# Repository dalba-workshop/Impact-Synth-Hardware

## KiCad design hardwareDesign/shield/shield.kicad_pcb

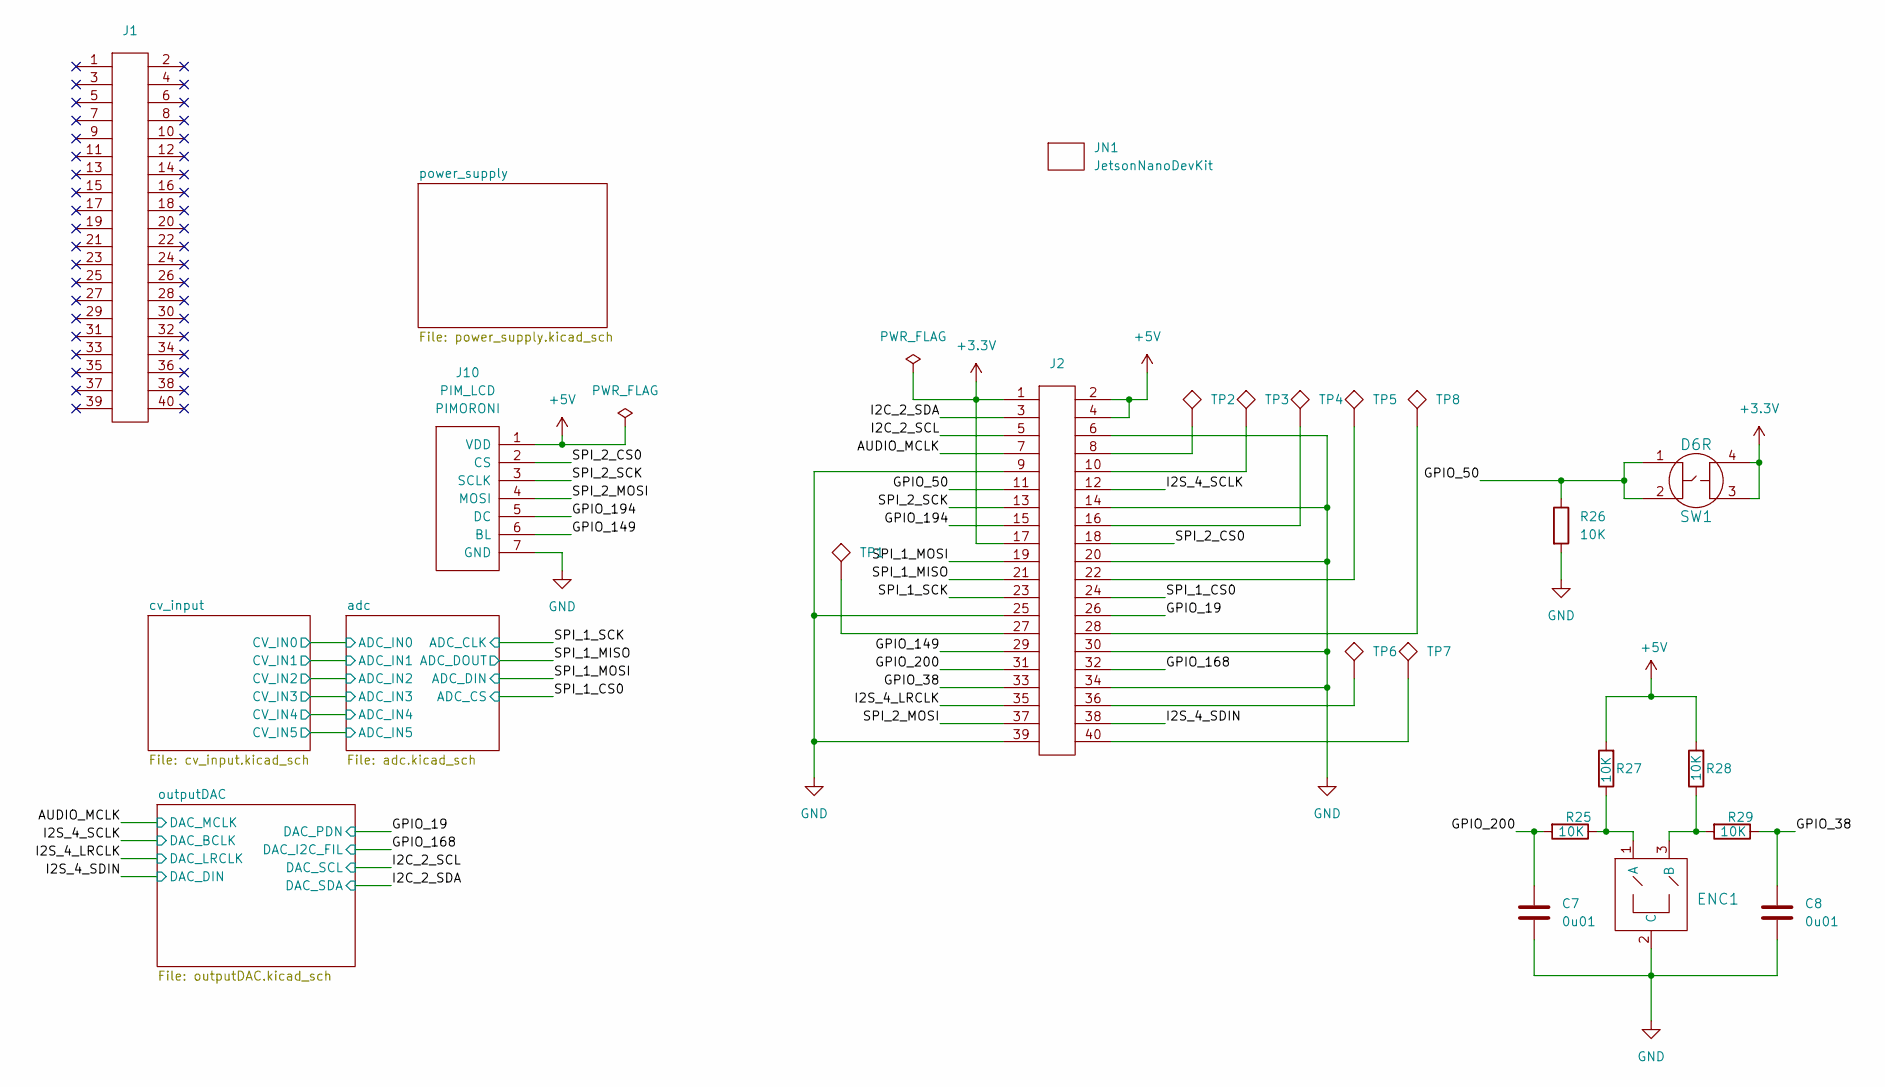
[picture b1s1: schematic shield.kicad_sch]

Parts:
C7, C8: 0.01uf_0603_50V; SMD_0603[1608]; Part Number VJ0603Y103KXACW1BC
ENC1: BOURNS_PEC11R_DET; BOURNS_ENCODER; Part Number PEC11R-4220F-N0024
J1: 40_POS_RIBBON; 40_POS_2.54mm; Part Number IDSD-20-D-04.00-T-G-RW
J2: 40_POS_Header; 40_POS_2.54mm; Part Number 10129381-940002BLF
J10: PIM_LCD; PIMORONI_LCD_240x240; Part Number PIMORONI_LCD_240x240
JN1: JetsonNano; jetsonNanoDev; Part Number RCG04021K00FKED
R25, R27, R28, R29: 10K_0603_2; SMD_0603[1608]; Part Number SFR03EZPF1002
R26: 10K_0603; SMD_0603[1608]; Part Number AC0603FR-0710KL
SW1: D6R; Part Number D6R60F1LFS
TP1, TP2, TP3, TP4, TP5, TP6, TP7, TP8: test_point_TH_Small; test_point_0.6mm

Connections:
+3V3: J2.1, J2.17, SW1.3, SW1.4; also elsewhere on the board
+5V: J2.2, J2.4, J10.1 (VDD), R27.2, R28.2; also elsewhere on the board
/AUDIO_MCLK: J2.7; also elsewhere on the board
/GPIO_19: J2.26; also elsewhere on the board
/GPIO_38: C8.1, J2.33, R29.1
/GPIO_50: J2.11, R26.1, SW1.1, SW1.2
/GPIO_149: J2.29, J10.6 (BL)
/GPIO_168: J2.32; also elsewhere on the board
/GPIO_194: J2.15, J10.5 (DC)
/GPIO_200: C7.1, J2.31, R25.2
/I2C_2_SCL: J2.5; also elsewhere on the board
/I2C_2_SDA: J2.3; also elsewhere on the board
/I2S_4_LRCLK: J2.35; also elsewhere on the board
/I2S_4_SCLK: J2.12; also elsewhere on the board
/I2S_4_SDIN: J2.38; also elsewhere on the board
/SPI_1_CS0: J2.24; also elsewhere on the board
/SPI_1_MISO: J2.21; also elsewhere on the board
/SPI_1_MOSI: J2.19; also elsewhere on the board
/SPI_1_SCK: J2.23; also elsewhere on the board
/SPI_2_CS0: J2.18, J10.2 (CS)
/SPI_2_MOSI: J2.37, J10.4 (MOSI)
/SPI_2_SCK: J2.13, J10.3 (SCLK)
GND: C7.2, C8.2, ENC1.2 (C), J2.6, J2.9, J2.14, J2.20, J2.25, J2.30, J2.34, J2.39, J10.7 (GND), R26.2; also elsewhere on the board
unnamed: ENC1.1 (A), R25.1, R27.1
unnamed: ENC1.3 (B), R28.1, R29.2
unnamed: J2.8, TP2.1
unnamed: J2.10, TP3.1
unnamed: J2.16, TP4.1
unnamed: J2.22, TP5.1
unnamed: J2.27, TP1.1
unnamed: J2.28, TP8.1
unnamed: J2.36, TP6.1
unnamed: J2.40, TP7.1

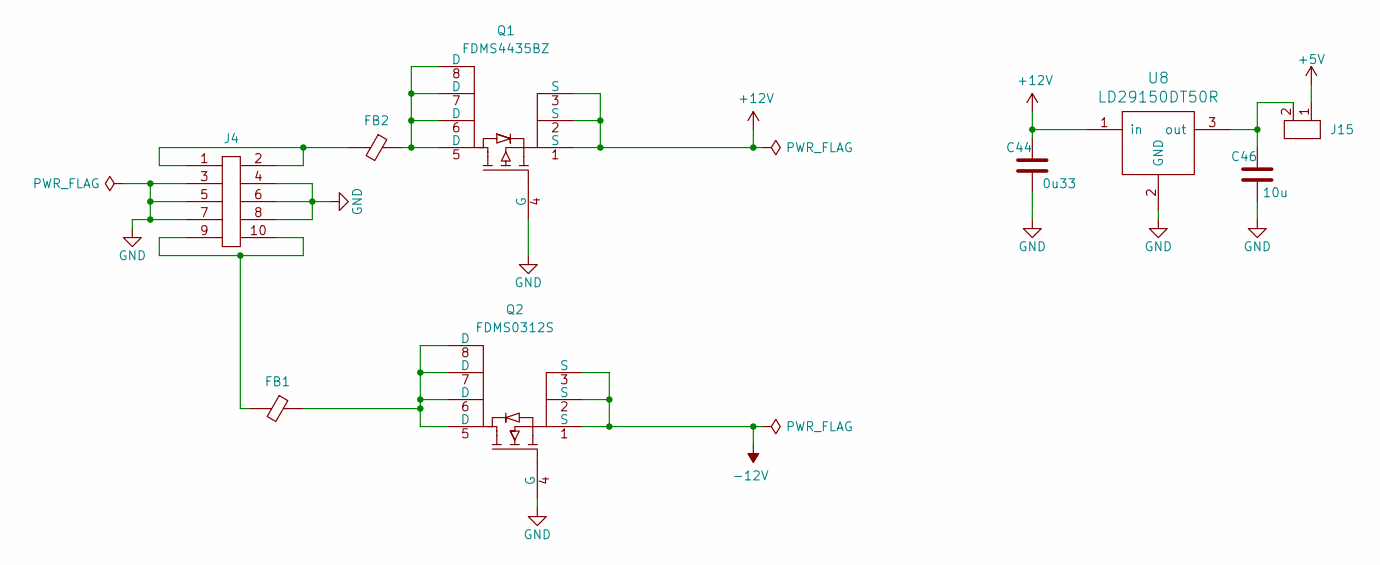
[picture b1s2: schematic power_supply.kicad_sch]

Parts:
C44: 0.33uf_0603_25V; SMD_0603[1608]; Part Number CC0603KRX7R8BB334
C46: 10uf_0603_25V; SMD_0603[1608]; Part Number GRT188R61E106ME13D
FB1, FB2: FB_HZ0805; Part Number HZ0805C202R-10
J4: 10_POS_PIN_HEADER_ALT; 05x02_2.54_pitch_pin_header; Part Number 61201021621
J15: 2x1_PIN_HEADER; 02x01_2.54_pitch_pin_header; Part Number 67996-400HLF
Q1: FDMS4435BZ; Power-56-8; Part Number FDMS4435BZ
Q2: FDMS0312S; Power-56-8; Part Number FDMS0312S
U8: LD29150DT50R; TO-252-3_ST; Part Number LD29150DT50R

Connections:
+5V: J15.1; also elsewhere on the board
+12V: C44.1, Q1.1 (S), Q1.2 (S), Q1.3 (S), U8.1 (in); also elsewhere on the board
-12V: Q2.1 (S), Q2.2 (S), Q2.3 (S); also elsewhere on the board
GND: C44.2, C46.2, J4.3, J4.4, J4.5, J4.6, J4.7, J4.8, Q1.4 (G), Q2.4 (G), U8.2 (GND); also elsewhere on the board
unnamed: C46.1, J15.2, U8.3 (out)
unnamed: FB1.1, Q2.5 (D), Q2.6 (D), Q2.7 (D), Q2.8 (D)
unnamed: FB1.2, J4.9, J4.10
unnamed: FB2.1, Q1.5 (D), Q1.6 (D), Q1.7 (D), Q1.8 (D)
unnamed: FB2.2, J4.1, J4.2

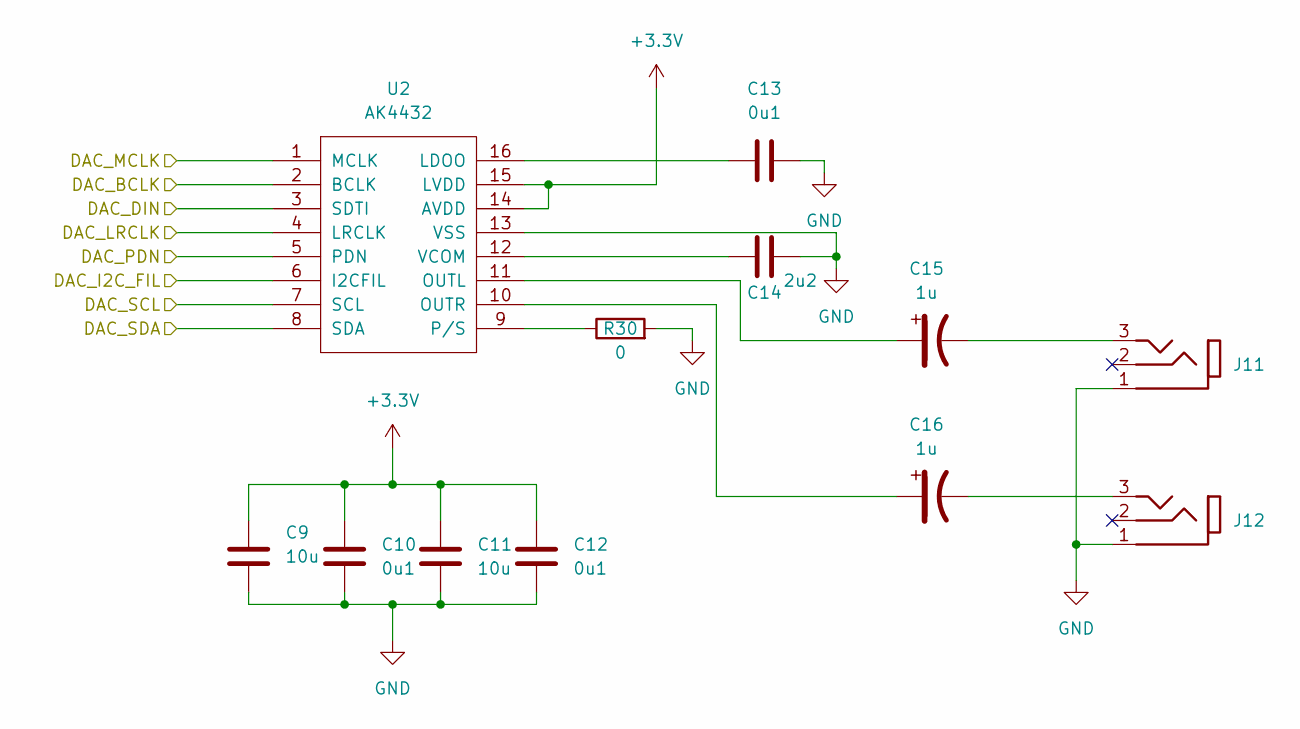
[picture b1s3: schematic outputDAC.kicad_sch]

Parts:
C9, C11: 10uf_0603_25V; SMD_0603[1608]; Part Number GRT188R61E106ME13D
C10, C12, C13: 0.1uf_0603_10V; SMD_0603[1608]; Part Number 885012206020
C14: 2.2uf_0603_10V; SMD_0603[1608]; Part Number 885012106011
C15, C16: 1uf_4.3mm_50V_POL_LP; WE_4mm_cap; Part Number RSVVS010M1UBC3001U
J11, J12: WQP419; Part Number WQP-WQP419GR
R30: 0_0603; SMD_0603[1608]; Part Number CRCW06030000Z0EAC
U2: AK4432; TSSOP-16; Part Number AK4432VT

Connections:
+3V3: C9.1, C10.1, C11.1, C12.1, U2.14 (AVDD), U2.15 (LVDD); also elsewhere on the board
/AUDIO_MCLK: U2.1 (MCLK); also elsewhere on the board
/GPIO_19: U2.5 (PDN); also elsewhere on the board
/GPIO_168: U2.6 (I2CFIL); also elsewhere on the board
/I2C_2_SCL: U2.7 (SCL); also elsewhere on the board
/I2C_2_SDA: U2.8 (SDA); also elsewhere on the board
/I2S_4_LRCLK: U2.4 (LRCLK); also elsewhere on the board
/I2S_4_SCLK: U2.2 (BCLK); also elsewhere on the board
/I2S_4_SDIN: U2.3 (SDTI); also elsewhere on the board
GND: C9.2, C10.2, C11.2, C12.2, C13.2, C14.1, J11.1, J12.1, R30.2, U2.13 (VSS); also elsewhere on the board
unnamed: C13.1, U2.16 (LDOO)
unnamed: C14.2, U2.12 (VCOM)
unnamed: C15.1, J11.3
unnamed: C15.2, U2.11 (OUTL)
unnamed: C16.1, J12.3
unnamed: C16.2, U2.10 (OUTR)
unnamed: R30.1, U2.9 (P/S)

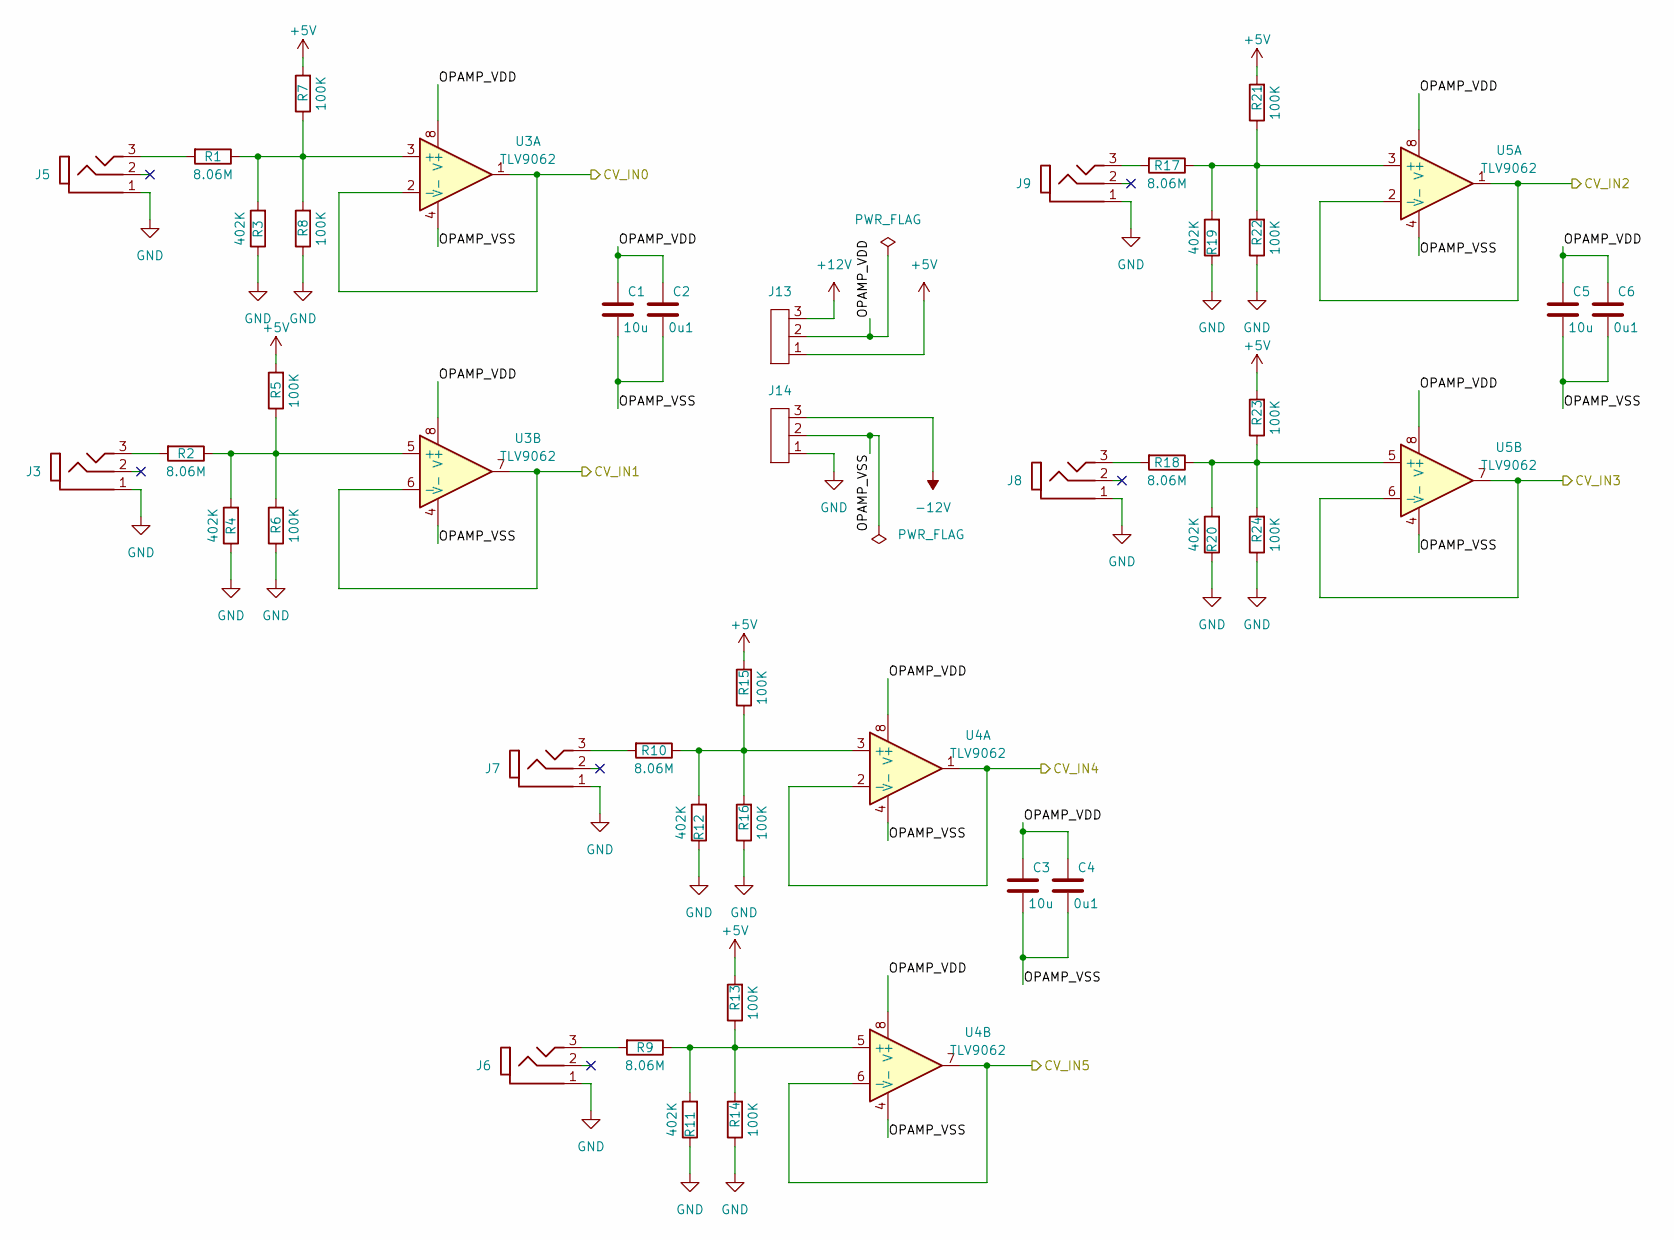
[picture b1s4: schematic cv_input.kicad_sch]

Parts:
C1, C3, C5: 10uf_0603_25V; SMD_0603[1608]; Part Number GRT188R61E106ME13D
C2, C4, C6: 0.1uf_0603_10V; SMD_0603[1608]; Part Number 885012206020
J3, J5, J6, J7, J8, J9: WQP419; Part Number WQP-WQP419GR
J13, J14: 3x1_PIN_HEADER; 03x01_2.54_pitch_pin_header; Part Number 10129378-903001BLF
R1, R2, R9, R10, R17, R18: 8.06M_0805; SMD_0805[2012]; Part Number RC0805FR-078M06L
R3, R4, R11, R12, R19, R20: 402K_0603; SMD_0603[1608]; Part Number RT0603FRE07402KL
R5, R6, R7, R8, R13, R14, R15, R16, R21, R22, R23, R24: 100K_0603; SMD_0603[1608]; Part Number ERJ-3EKF1003V
U3, U4, U5: TLV9062; SOT23-8; Part Number TLV9062IDDFR

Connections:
+5V: J13.1, R5.2, R7.2, R13.2, R15.2, R21.2, R23.2; also elsewhere on the board
+12V: J13.3; also elsewhere on the board
-12V: J14.3; also elsewhere on the board
/adc/ADC_IN0: U3.1, U3.2 (-); also elsewhere on the board
/adc/ADC_IN1: U3.6 (-), U3.7; also elsewhere on the board
/adc/ADC_IN2: U5.1, U5.2 (-); also elsewhere on the board
/adc/ADC_IN3: U5.6 (-), U5.7; also elsewhere on the board
/adc/ADC_IN4: U4.1, U4.2 (-); also elsewhere on the board
/adc/ADC_IN5: U4.6 (-), U4.7; also elsewhere on the board
/cv_input/OPAMP_VDD: C1.1, C2.1, C3.1, C4.1, C5.1, C6.1, J13.2, U3.8 (V+), U4.8 (V+), U5.8 (V+)
/cv_input/OPAMP_VSS: C1.2, C2.2, C3.2, C4.2, C5.2, C6.2, J14.2, U3.4 (V-), U4.4 (V-), U5.4 (V-)
GND: J3.1, J5.1, J6.1, J7.1, J8.1, J9.1, J14.1, R3.1, R4.1, R6.1, R8.1, R11.1, R12.1, R14.1, R16.1, R19.1, R20.1, R22.1, R24.1; also elsewhere on the board
unnamed: J3.3, R2.2
unnamed: J5.3, R1.2
unnamed: J6.3, R9.2
unnamed: J7.3, R10.2
unnamed: J8.3, R18.2
unnamed: J9.3, R17.2
unnamed: R1.1, R3.2, R7.1, R8.2, U3.3 (+)
unnamed: R2.1, R4.2, R5.1, R6.2, U3.5 (+)
unnamed: R10.1, R12.2, R15.1, R16.2, U4.3 (+)
unnamed: R9.1, R11.2, R13.1, R14.2, U4.5 (+)
unnamed: R17.1, R19.2, R21.1, R22.2, U5.3 (+)
unnamed: R18.1, R20.2, R23.1, R24.2, U5.5 (+)

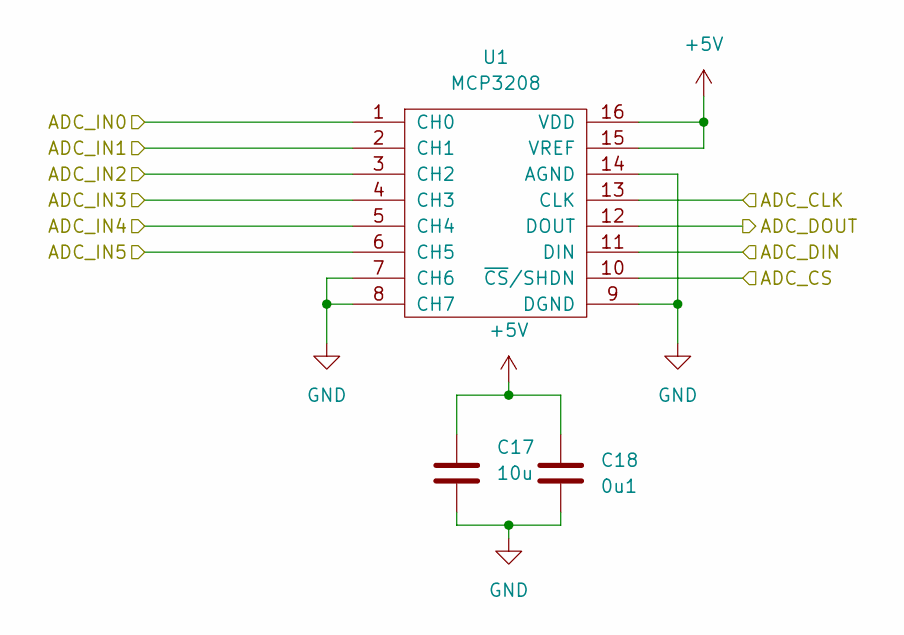
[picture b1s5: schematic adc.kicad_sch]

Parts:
C17: 10uf_0603_25V; SMD_0603[1608]; Part Number GRT188R61E106ME13D
C18: 0.1uf_0603_10V; SMD_0603[1608]; Part Number 885012206020
U1: MCP3208; SOIC-16; Part Number MCP3208-CI/SL

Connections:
+5V: C17.1, C18.1, U1.15 (VREF), U1.16 (VDD); also elsewhere on the board
/SPI_1_CS0: U1.10 (~CS/SHDN); also elsewhere on the board
/SPI_1_MISO: U1.12 (DOUT); also elsewhere on the board
/SPI_1_MOSI: U1.11 (DIN); also elsewhere on the board
/SPI_1_SCK: U1.13 (CLK); also elsewhere on the board
/adc/ADC_IN0: U1.1 (CH0); also elsewhere on the board
/adc/ADC_IN1: U1.2 (CH1); also elsewhere on the board
/adc/ADC_IN2: U1.3 (CH2); also elsewhere on the board
/adc/ADC_IN3: U1.4 (CH3); also elsewhere on the board
/adc/ADC_IN4: U1.5 (CH4); also elsewhere on the board
/adc/ADC_IN5: U1.6 (CH5); also elsewhere on the board
GND: C17.2, C18.2, U1.7 (CH6), U1.8 (CH7), U1.9 (DGND), U1.14 (AGND); also elsewhere on the board

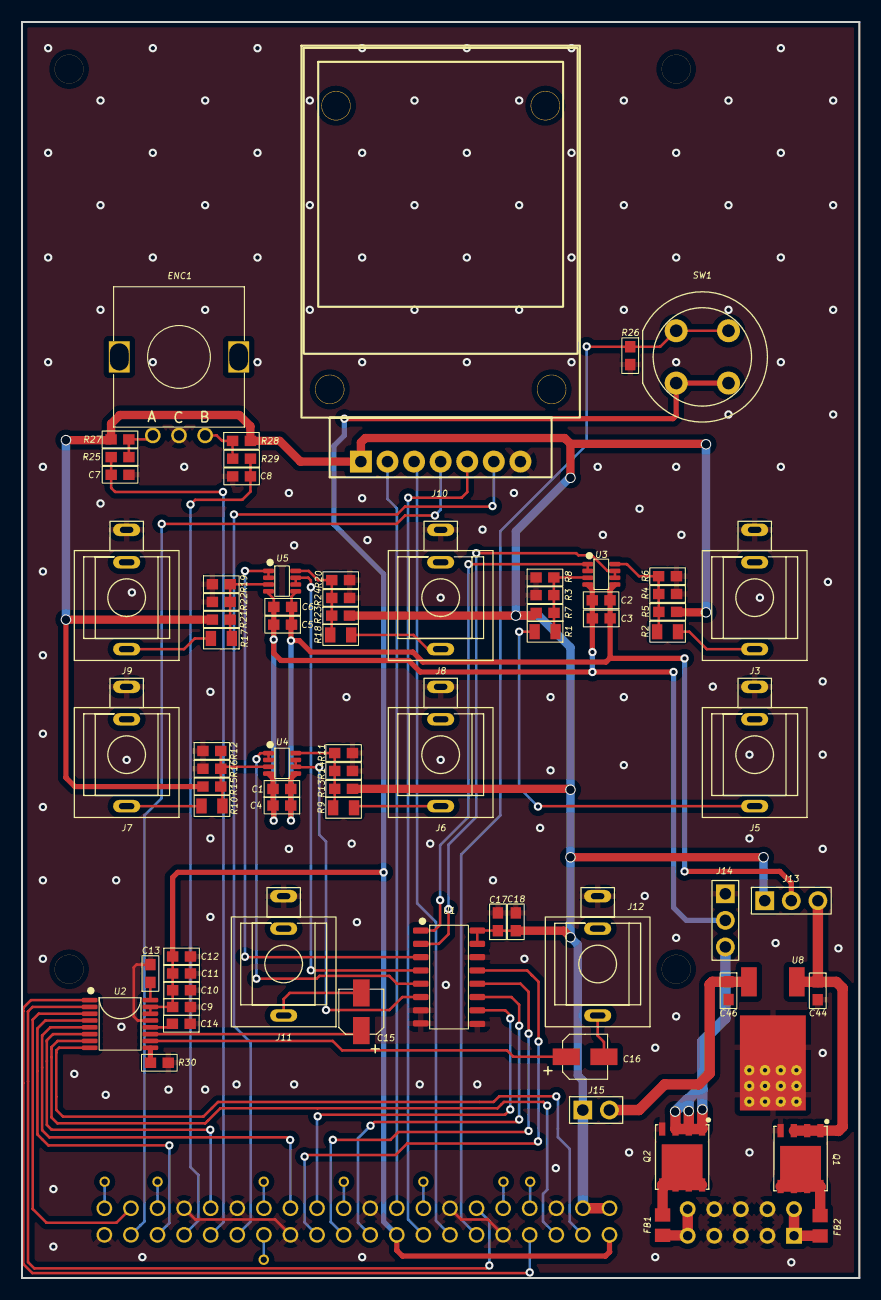
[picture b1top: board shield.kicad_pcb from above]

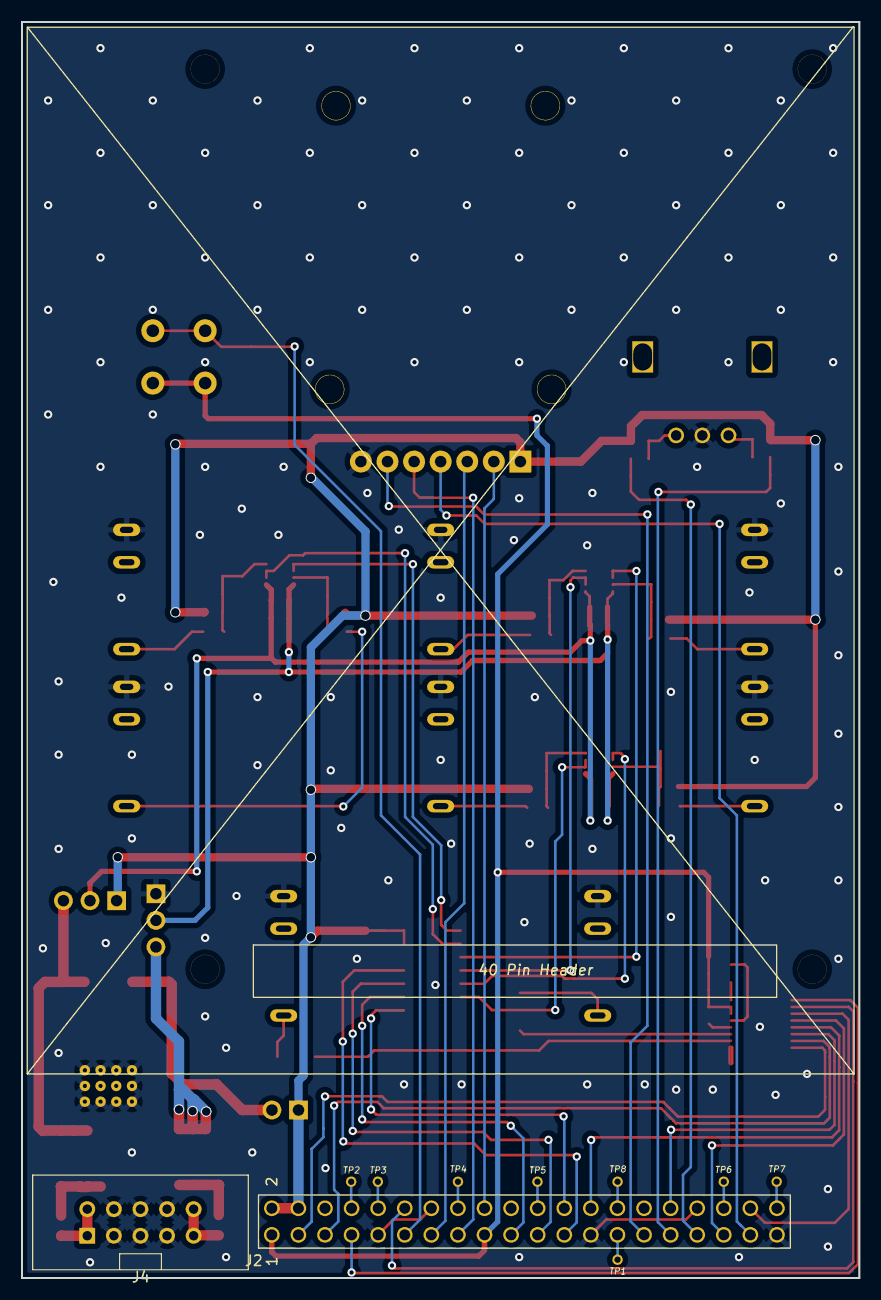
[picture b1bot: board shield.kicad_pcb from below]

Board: 2 copper layers, 80.0 x 120.0 mm, 85 parts (11 on the bottom side), 67 nets.

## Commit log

2022-12-22 org notes file added
2022-12-26 Added datasheets, started hardware deign
2022-12-31 Schematic done
2023-01-07 Finished schematic and PCB for jetson Nano Sheild
2023-01-10 Board layout done and parts ordered
2023-01-11 Finished layout with JN real footprint
2023-01-12 Checked mechanica fit
2023-01-22 fab files
2023-01-26 Created 3d model for case
2023-02-05 typo in readme
